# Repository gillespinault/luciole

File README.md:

# Luciole²

Lumières de vélo qui se parlent. Un essaim de petites unités (M5Stack NanoC6 ou AtomS3 Lite, ruban de LED SK6812) qui se découvrent par radio ESP-NOW longue portée, sans coordinateur ni réseau, et qui montrent d'un coup d'œil si on roule seul ou ensemble. Première sortie : Critical Mass de Bruxelles, 30 octobre 2026, avec les Merveilleux Fous Roulants.

| Dossier | Contenu |
|---|---|
| `firmware/` | Firmware ESP-IDF, une image par puce, nombre de LED en configuration. Voir `firmware/README.md`. |
| `web/` | Site public https://lucioles.limn-labs.xyz, publié par GitHub Pages à chaque push sur `main` : présentation, installation par USB depuis le navigateur (ESP Web Tools), page du maître `maitre/` (scènes : équipes, vote, jauge), page de mise au point `luciole/` (état en direct, graphes, réglages, enregistrement CSV, sur ordinateur et Android), simulation. |
| `sim/` | Simulation d'un Critical Mass : 20 000 vélos, 1 000 lucioles, mêmes règles que le firmware. Un fichier HTML, à ouvrir tel quel. |

Documentation du projet : wiki Outline, collection Luciole² (journal, décisions, architecture et contrat radio, matériel).

## Installer une luciole

Ouvrir https://lucioles.limn-labs.xyz dans Chrome ou Edge sur un ordinateur, brancher la luciole en USB, choisir le nombre de LED, cliquer sur Installer. Les mises à jour se font de la même façon.

En local, sans GitHub Pages : compiler (`firmware/README.md`), puis

```bash
python3 web/build.py --local          # assemble web/firmware/ (binaires, configurations NVS, manifestes)
python3 -m http.server 8766 --directory web
```

Web Serial exige HTTPS ou `localhost` : pour flasher depuis un autre poste, il faut passer par la page publiée.

## Régler une luciole sans la reflasher

https://lucioles.limn-labs.xyz/luciole/ : la luciole branchée en USB envoie son état en JSON (commande `stream`) et accepte `set clé valeur` pour chacun de ses 14 réglages, enregistrés en NVS. La page trace le signal des voisines, l'état, la phase, la radio et les ondes ; enregistre en CSV avec GPS ; gère des profils. Sur Android, elle parle à la luciole par WebUSB avec sa propre couche CDC (le Web Serial de Chrome Android ne sait pas ouvrir un appareil USB). Détail des commandes dans `firmware/README.md`.

## Faire évoluer le firmware sans casser l'essaim

Le contrat radio v1 (`firmware/main/luciole.h`, section « Contrat radio ») fixe le canal, le mode longue portée, le cycle de 2,5 s et le format des trames. Une luciole déjà distribuée doit rester membre de l'essaim : les nouveaux champs vont en fin de trame, les octets inconnus sont ignorés, la trame d'onde ne se remplace jamais. Le rendu (arc-en-ciel, cœur, couleurs, onde) est local et change librement. Vérifier les changements d'échelle dans `sim/index.html` avant de flasher.

## Licence

Luciole² est publié sous [CC BY-NC-SA 4.0](https://creativecommons.org/licenses/by-nc-sa/4.0/deed.fr) : réutilisation et modification libres avec attribution, partage à l'identique, pas d'usage commercial. Texte complet dans `LICENSE`.

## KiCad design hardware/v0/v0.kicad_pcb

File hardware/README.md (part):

# Cartes électroniques de Luciole²

Les cartes sont décrites par des scripts. Une commande reconstruit le schéma, la carte et les fichiers à déposer chez JLCPCB :

    tools/build.sh essai

Il faut Docker et l'image `kicad/kicad:10.0.8-full`. Le lanceur `tools/kicad` la désigne par son empreinte : la version de KiCad ne change pas tant que ce fichier ne change pas.

La spécification de la carte v0 et la méthode sont dans la collection Luciole² du wiki, pages « Carte Luciole² v0 » et « Conception de la carte v0 ».

## Dossiers

| Dossier | Contenu |
|---------|---------|
| `tools/` | La chaîne d'outils, commune à toutes les cartes |
| `lib/` | Les symboles et empreintes absents de la bibliothèque de KiCad, ou dont le brochage diffère. `build_lib.py` les écrit à partir des cotes des fiches techniques |
| `essai/` | Carte d'essai : trois LED entre deux connecteurs Grove, une pastille de test et un condensateur au dos. Elle a servi à valider la chaîne et la pose chez JLCPCB, et reste le banc de la chaîne |
| `v0/` | Carte v0, 122 × 28 mm, deux couches. La liste de connexions voulue et le schéma, révision 0.6, concordent : 160 composants, 85 réseaux. La carte est tracée en entier depuis le 18 novembre 2026 : `tools/build.sh v0` va au bout, sans liaison manquante ni alerte hors dérogations. Le tracé est figé dans `v0/routage.json`. Deux modèles l'ont relu le 18 novembre : huit corrections sont faites et contre-relues (dossier dans `v0/revue/`). Le brochage des 27 pièces autres que résistances et condensateurs a été relevé à l'aveugle dans les fiches des pièces commandées, et l'orientation de chaque pièce contrôlée dans l'aperçu de pose de JLCPCB. Le schéma a été comparé aux montages de référence et simulé, puis la carte confrontée aux retours d'expérience d'autres concepteurs. Rien n'est commandé |
| `fiches/` | Fiches techniques des fabricants et pièces de preuve. Gardées en local, non suivies par git ; `fiches/README.md` donne leurs sources |

## Les quatre fichiers d'une carte

Une carte est un dossier qui contient quatre fichiers écrits à la main.

`netlist_voulue.txt` donne les connexions voulues, par numéros de broches lus dans les fiches techniques. Il s'écrit avant le schéma. Une ligne qui commence par un espace continue le réseau de la ligne précédente.

`empreintes_voulues.txt` donne la géométrie voulue de chaque empreinte : le centre, la taille et le numéro de chaque pastille, relevés sur le plan du fabricant. Un boîtier normalisé pris dans la bibliothèque de KiCad s'y déclare `normalisé`, sans cotes.

`circuit.py` décrit le schéma, par noms de broches. Chaque broche doit être reliée à un réseau ou marquée `NC`, sinon la génération s'arrête. Elle s'arrête aussi quand deux composants sont posés si près que les fils de deux réseaux se touchent sur la page. Une empreinte sans pièce à poser (pastille de test, pont de soudure) se déclare avec `assemble=False`, une pièce prévue mais non montée avec `dnp=True`.

`carte.py` pose les composants et trace les pistes, en millimètres depuis le coin haut gauche de la carte. `flow()` range les petits composants d'un bloc dans un rectangle, `netclass()` donne leur largeur aux pistes d'alimentation. Un composant se pose au dos avec `bottom=True`. Son sens se vérifie par une assertion sur la position de ses pastilles, comme le fait la carte d'essai.

Les fichiers `.kicad_sch` et `.kicad_pcb` sont produits par ces scripts. Ils s'ouvrent dans KiCad pour la relecture. Une modification faite à la main dans KiCad est perdue à la construction suivante : elle se reporte dans le script.

## Étapes de la construction

1. Écriture de la bibliothèque du projet.
2. Écriture du schéma.
3. Contrôle électrique du schéma par KiCad.
4. Comparaison, broche par broche, de `netlist_voulue.txt` avec les connexions que KiCad exporte du schéma.
5. Comparaison, pastille par pastille, de `empreintes_voulues.txt` avec les fichiers d'empreintes.
6. Écriture de la carte à partir des connexions exportées.
7. Contrôle des règles de dessin par KiCad, avec la cohérence entre carte et schéma. KiCad remplit lui-même les plans de masse à cette étape. Toute alerte arrête la construction, sauf dérogation écrite dans `<projet>/derogations.txt`, avec sa raison ; `out/drc-compte-rendu.txt` sépare ce qui est ignoré de ce qui reste.
8. Export des fichiers de fabrication et des documents de relecture.

La construction s'arrête à la première étape qui échoue. L'étape 4 est celle qui attrape un symbole au mauvais brochage : le contrôle électrique de KiCad ne le voit pas. L'étape 5 attrape une empreinte mal numérotée ou mal cotée, que le contrôle des règles de dessin ne voit pas non plus dès que la carte est routée par réseau.

La pose d'une empreinte s'arrête aussi dans trois cas. Une pastille numérotée n'a pas de broche dans le schéma : c'est une plage thermique ou un blindage oubliés dans le symbole, ou alors une pastille à déclarer libre avec `free_pads`. Une broche laissée libre correspond à plusieurs pastilles de même numéro : il faut les relier à un réseau. Un symbole a plusieurs unités : la chaîne ne les gère pas, on dessine un symbole à une seule unité dans `lib/build_lib.py`.

Deux constructions de suite donnent les mêmes fichiers, à la date près dans les en-têtes.

Les fichiers KiCad du projet sont supprimés au début de chaque construction, fichier de projet compris. Un réglage fait à la main dans KiCad, comme la désactivation d'un contrôle, ne survit donc pas. Les verrous (`~projet.kicad_pro.lck`) sont supprimés aussi : un verrou resté d'une session interrompue fait croire à KiCad que le projet est ouvert ailleurs, il n'écrit alors plus le fichier de projet et la carte échoue à l'écriture des classes de réseaux.

## Routage

Le routage d'une carte se fait en deux temps, tous deux dans `carte.py`.

La structure se trace par script : liaisons longues, alimentations, convertisseur, sorties des boîtiers à pas fin. C'est elle qui décide si la carte est routable. L'en-tête de `v0/carte.py` décrit le plan retenu pour la carte v0.

Les petits composants sont posés par `tools/pose.py` : chacun va à la place libre la plus proche du cuivre que ses pastilles relient, dans l'orientation qui convient. Les ranger par rangées, sans regarder leurs connexions, donnait des blocs où tout devait se croiser.

Les liaisons courtes qui restent, autour de chaque bloc, sont tracées par le routeur sur grille `tools/maille.py`, puis figées dans `<projet>/routage.json` :

    tools/kicad python3 v0/carte.py --router
    tools/kicad python3 v0/carte.py --router --reseaux=EN,BOOT    # quelques réseaux, pour mettre au point un bloc

La construction normale rejoue ce fichier. Sa signature dit pour quelle carte il a été calculé : après un changement de placement ou de structure, la construction s'arrête et demande de relancer le routeur.

Le routeur sur grille applique nos règles d'isolement, sur une grille de 0,05 mm, à 45 degrés, sur deux faces. Quand une liaison ne passe pas, il défait les pistes qu'il a lui-même tracées et qui la barrent, la trace, puis retrace les réseaux défaits. Il ne touche jamais aux pistes tracées par script. Il redonne toujours le même tracé. Il signale les alimentations qu'il a dû tracer plus fin que leur classe. Une pastille ni rectangulaire ni ronde (pont de soudure, pastille aux coins arrondis) est prise avec son contour exact : une piste arrêtée dans un coin de son rectangle englobant n'y est pas reliée, pour KiCad.

Une fois la carte tracée, `carte.py` fait deux finitions, à chaque construction.

La masse d'abord. Sur deux couches, chaque piste coupe un plan, et les deux plans finissent en morceaux. `Board.stitch_zones()` regroupe les morceaux déjà reliés entre eux, puis pose un via là où un morceau isolé recouvre le plan principal de l'autre face. Un morceau sans recouvrement est enfermé entre des pistes : `Router.tie()` relie alors une de ses pastilles au cuivre de masse principal, comme le routeur trace un signal, par l'une ou l'autre face. Ce qui reste isolé après cela est affiché, avec ses pastilles : c'est une poche sans issue, qui se règle dans la structure, en donnant un via de masse au composant avant le routage.

L'ébarbage ensuite. La structure propose des accès que le routeur n'utilise pas tous : un via au bout d'une voie, une sortie devant une pastille à pas fin. `Board.trim()` demande à KiCad quels bouts de piste et quels vias sont pendants, par le test de son propre contrôle. Il raccourcit la piste jusqu'à son dernier raccord, ou la retire. Avant de retirer un via relié sur une seule face, il prolonge jusqu'à son centre les pistes qui finissaient dans sa pastille : c'est le cuivre du via qui les reliait. `--sans-ebarbage` saute cette étape, pour regarder la carte avant.

Pour voir un blocage, `tools/vue.py` dessine une zone de la carte avec le nom du réseau sur chaque pastille :

    tools/kicad python3 tools/vue.py v0/v0.kicad_pcb 92 13 117 28 --face=F --reseaux=PORT_PU,IO2
    tools/kicad python3 tools/vue.py v0/v0.kicad_pcb 19 19 40 28 --face=B --plans

`--reseaux` met ces réseaux en couleurs vives, `--plans` dessine le cuivre des plans de masse : un morceau isolé s'y voit tout de suite.

Pour comparer des variantes sans toucher au projet, `v0/carte.py` accepte des options d'essai. Avec l'une d'elles, la carte et son tracé s'écrivent dans `v0/out/`, sous un nom qui dit la variante ; plusieurs essais peuvent tourner en même temps.

    tools/kicad python3 v0/carte.py --router --largeur=28 --graine=7

| Option | Effet |
|--------|-------|
| `--largeur=28` | Largeur de la carte. Elle s'élargit par le bas : la rangée de LED, le module et les connecteurs gardent leur place |
| `--graine=7` | Autre ordre de passage du routeur. Chaque graine donne un autre tracé ; une graine donnée redonne le même |
| `--ecart=0.35` | Écart que le poseur laisse entre deux composants (0,2 mm par défaut) |
| `--dos=1` | Surcoût d'une piste nouvelle au dos, sous la batterie (3 par défaut) |
| `--sans=SW1,SW2` | Ne pose pas ces composants, pour mesurer ce que leur retrait libère sans toucher au schéma |

`--graine` seule n'ouvre pas le mode d'essai : elle sert aussi à tracer la carte du projet avec l'ordre retenu.

### Ce que les essais du 18 novembre 2026 ont appris

- La largeur compte plus que tout le reste. Avec toutes les fonctions, le routeur laisse 26 liaisons à 22 mm, 19 à 24 mm, 15 à 26 mm, 5 à 28 mm et 4 à 30 mm. La carte est passée à 28 mm.
- Retirer les boutons internes ne change rien. Lever le surcoût du dos non plus : les blocs qui coincent sont là où le dos est déjà pris. Un écart du poseur de 0,35 ou 0,5 mm fait moins bien que 0,2 mm.
- Lancer le routeur avec une douzaine de graines dit où chercher. Une liaison qui échoue à un endroit différent selon la graine relève de l'ordre de passage. Un réseau qui échoue à toutes les graines désigne une erreur de structure : une piste tracée par script qui enferme d'autres signaux. La commande du convertisseur, tracée en face avant devant le module, enfermait ainsi la donnée des LED et les sorties de la colonne de gauche ; elle passe maintenant au dos, dans le faisceau.
- Une protection à deux pastilles par ligne (USBLC6) se relie sous son boîtier, par script. Laissé seul, le routeur y croisait les deux lignes.
- Le poseur ne remplace pas un plan de bloc. Il met chaque composant au plus près de son cuivre, sans voir l'ordre dans lequel les signaux arrivent. Autour d'un transistor ou d'un circuit, les broches se suivent toujours dans le même sens : si les pistes arrivent dans l'autre, il faut un croisement, donc un via, et il n'y a pas toujours la place. Les blocs où plusieurs signaux se partagent quelques composants sont donc posés et reliés par script : port côté module, USB, protecteur du port, résistances du chargeur, ponts de mesure. Le lot de douze graines est passé de zéro tracé complet à douze sur douze, et de vingt minutes à trois.
- Des voies qui remontent côte à côte forment un nid : de l'intérieur, seule la plus intérieure est accessible. Chaque voie du faisceau finit maintenant là où est son composant.
- Entre deux lignes qui traversent un composant, ce qui est au milieu est enfermé. Pour un protecteur USBLC6, c'est sa broche de masse d'un côté et sa broche d'alimentation de l'autre : il leur faut un via chacune, à un endroit où l'autre face est libre.
- L'USB-C et le Grove sont dos à dos : entre eux, presque aucun via n'est possible. Le bloc de l'USB est tracé pour s'en passer, et les broches CC passent sous la coque du connecteur.
- Une piste d'alimentation tracée en face avant coupe la bande qu'elle traverse. Les signaux qui doivent la franchir passent par le dos ; il faut donc y garder un passage libre, et y ranger les voies au ras du faisceau.
- La zone de garde du module radio a la forme d'un T, boîtier puis zone d'antenne. Prise pour un rectangle, elle interdisait tout le coin de la carte au poseur : `Board.courtyard_boxes()` la découpe suivant ses arêtes.
- La largeur de 28 mm a libéré deux zones que les régions du poseur, écrites pour 22 mm, n'utilisaient pas : sous le coin du module, sur les deux faces, et le milieu de la bande du bas.

### Ce que la revue du routage du 18 novembre 2026 a appris

Le tri complet est dans le wiki, page « Revue du routage du 18 novembre 2026 ».

- Le contrôle des règles ne voit pas les chemins. Un circuit de puissance sans via sous sa plage thermique, une ligne qui se sépare avant sa protection, un condensateur d'alimentation à 59 mm de la broche qu'il découple : tout cela passait le contrôle.
- Une protection contre les décharges se traverse. La ligne entre par une broche et repart de l'autre. Si elle se sépare avant, la décharge prend aussi le chemin qui évite la protection.
- Un circuit de puissance qui chauffe reçoit ses vias sous sa plage centrale au moment où on le pose, pas après.
- Poser par script les petits composants d'une commande de grille. Laissés au poseur, ceux de la protection contre l'inversion avaient donné 36 mm de piste et six vias pour deux pastilles distantes de 10 mm.
- Une piste courte entre deux grandes pastilles ne chauffe presque pas : la chaleur part par ses deux bouts. Les abaques de largeur supposent une piste longue. Chiffrer avant de redessiner un bloc.
- Toute piste ajoutée en face avant peut fermer une poche du plan de masse. Le compte des groupes restés isolés, à la fin de chaque essai, l'a signalé aux douze graines pour une correction mal placée.
- Un relecteur se trompe aussi. Sur trente constats, trois reposaient sur une lecture fausse des pièces ou de la nomenclature. Chaque constat se vérifie sur la carte avant d'être corrigé.

### Simulations

    v0/simu/lancer.sh            alimentation : inversion de la batterie, partage USB/batterie, chargeur
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
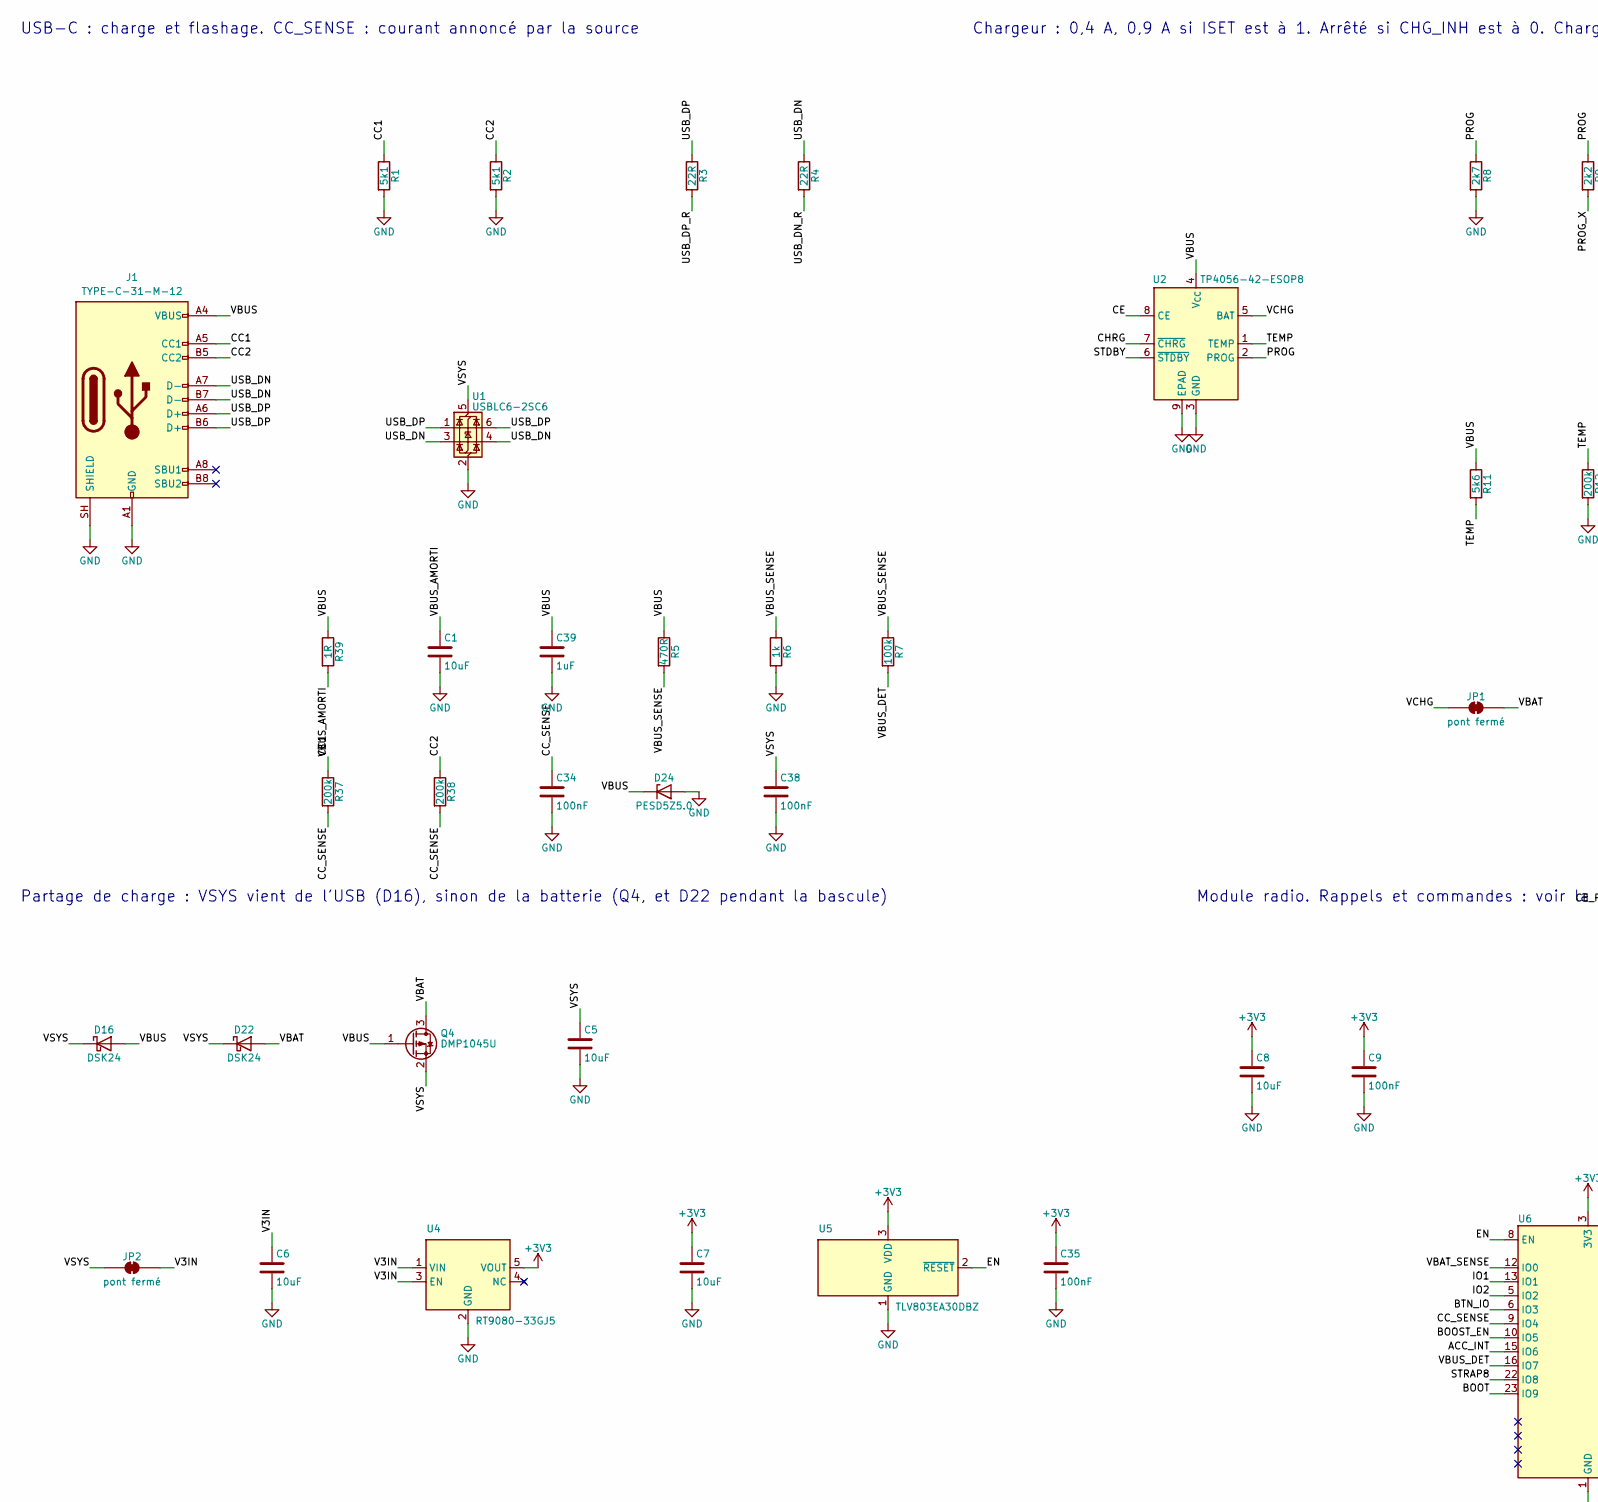
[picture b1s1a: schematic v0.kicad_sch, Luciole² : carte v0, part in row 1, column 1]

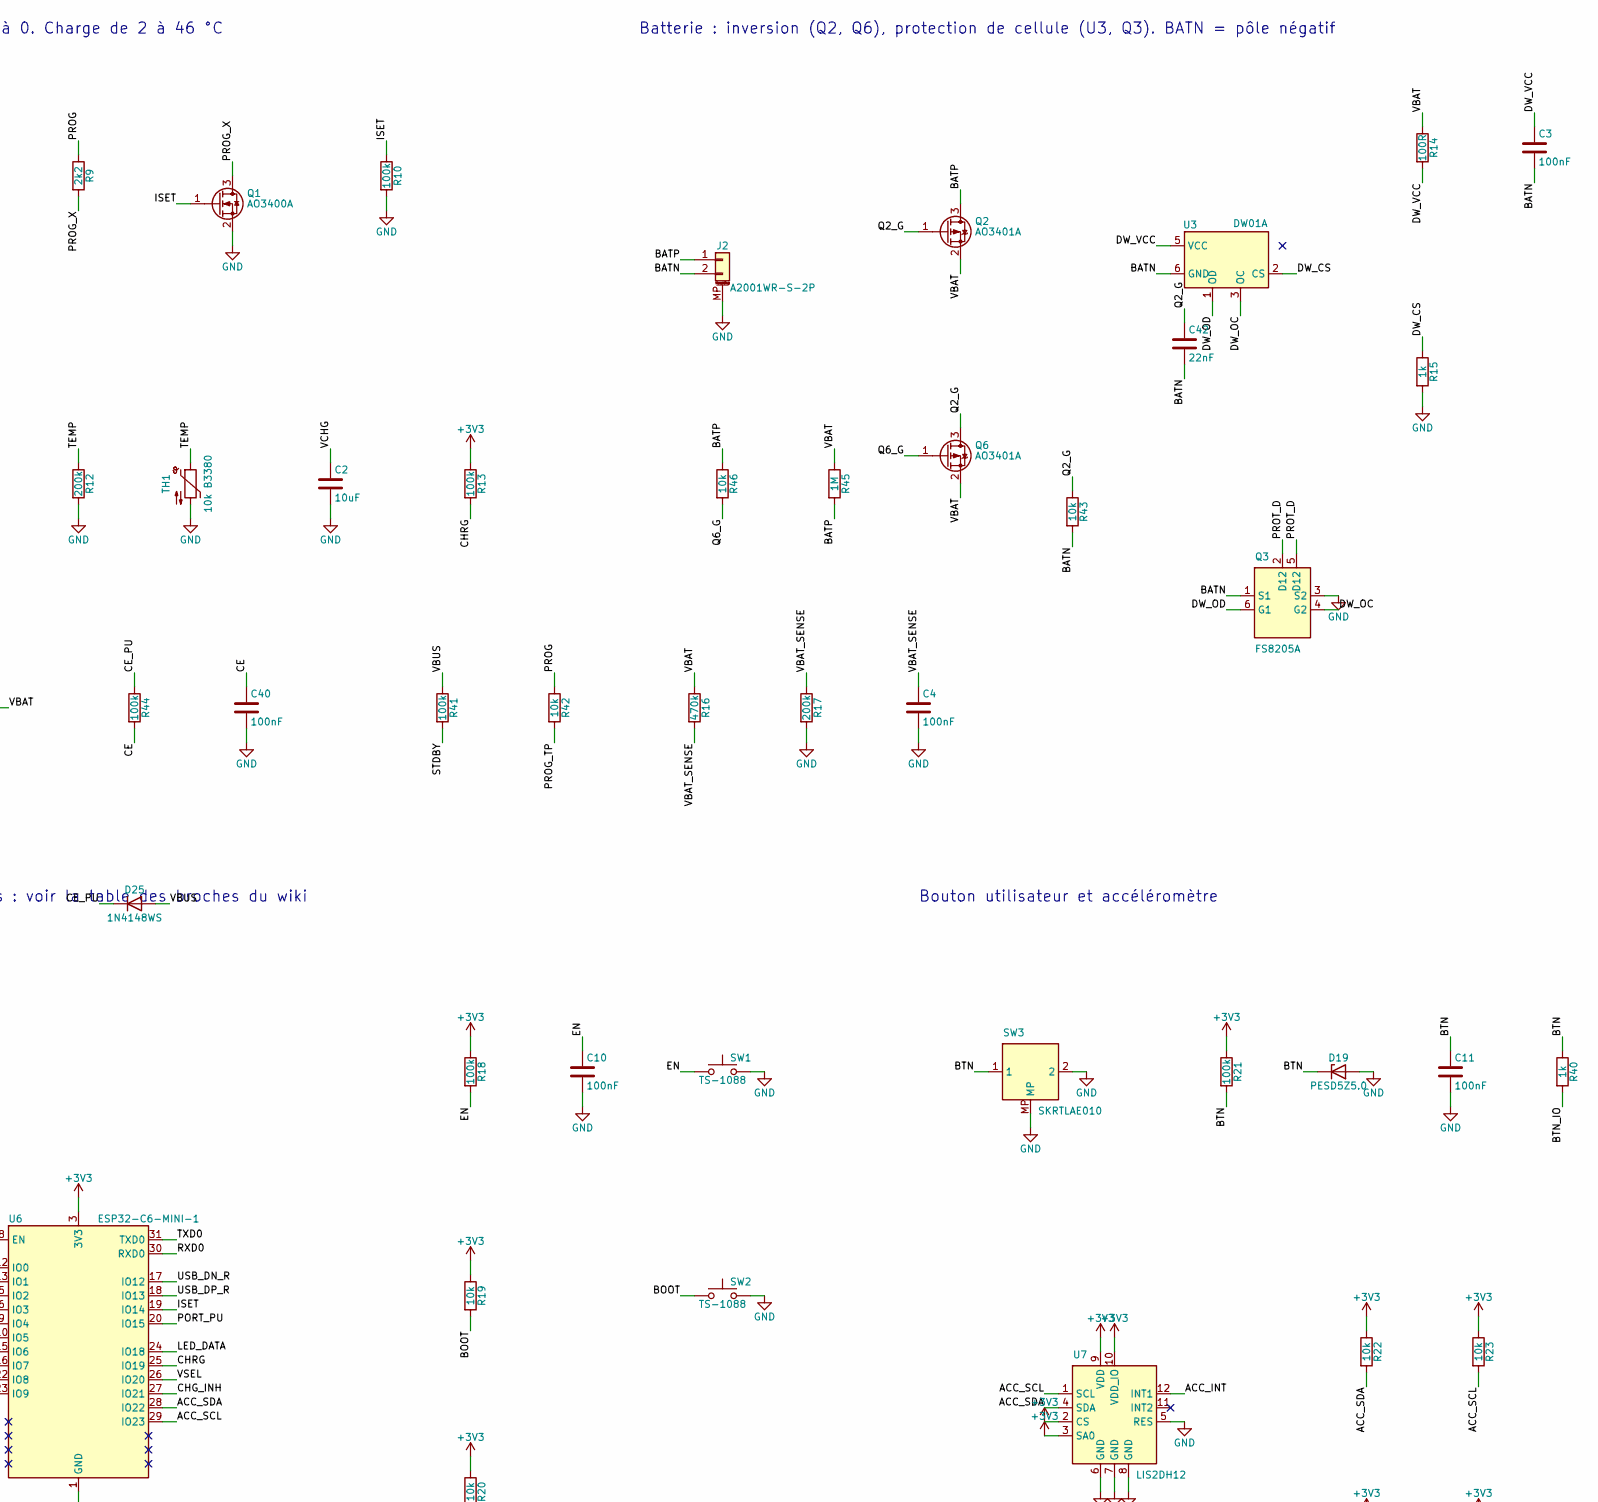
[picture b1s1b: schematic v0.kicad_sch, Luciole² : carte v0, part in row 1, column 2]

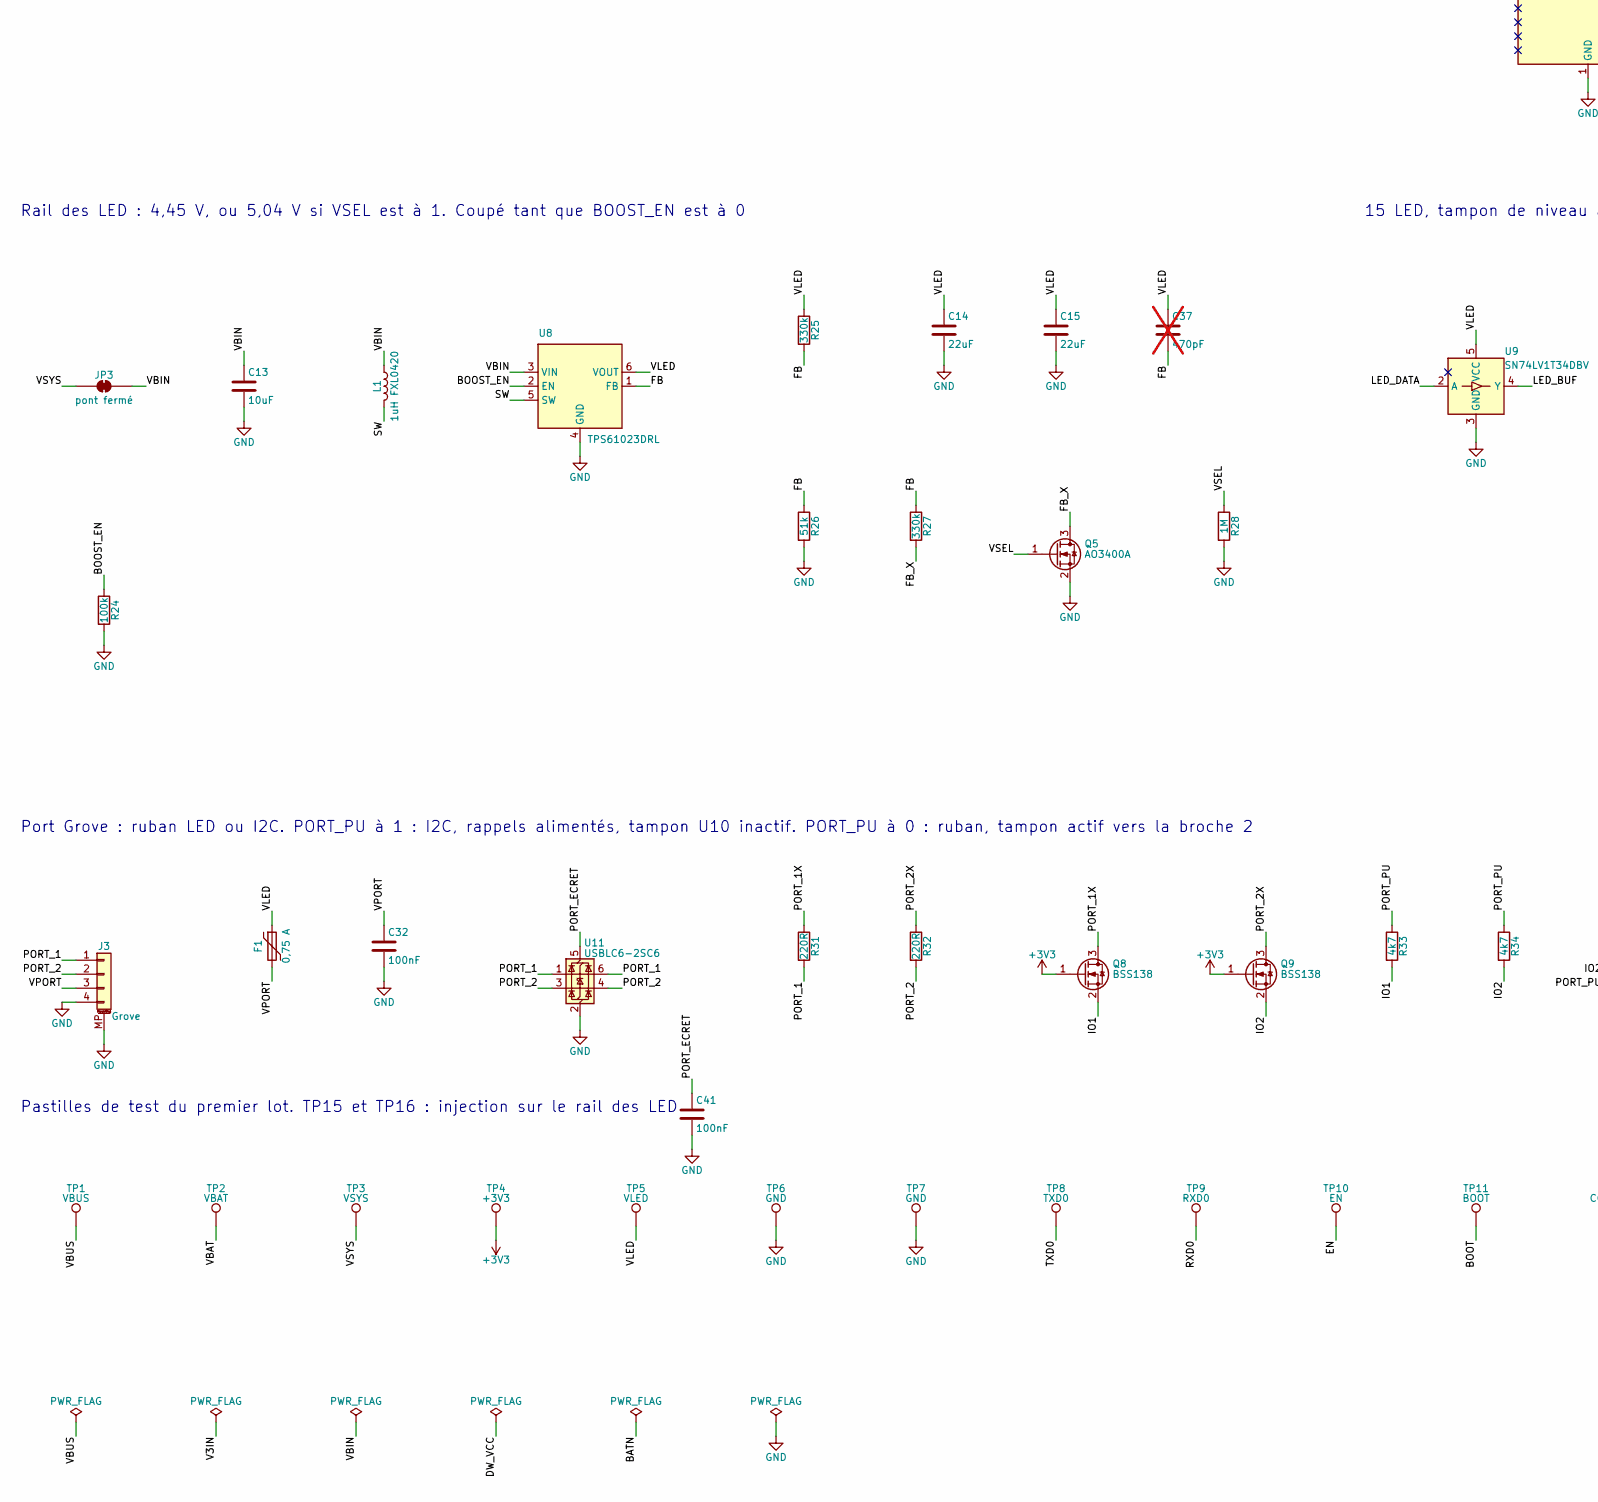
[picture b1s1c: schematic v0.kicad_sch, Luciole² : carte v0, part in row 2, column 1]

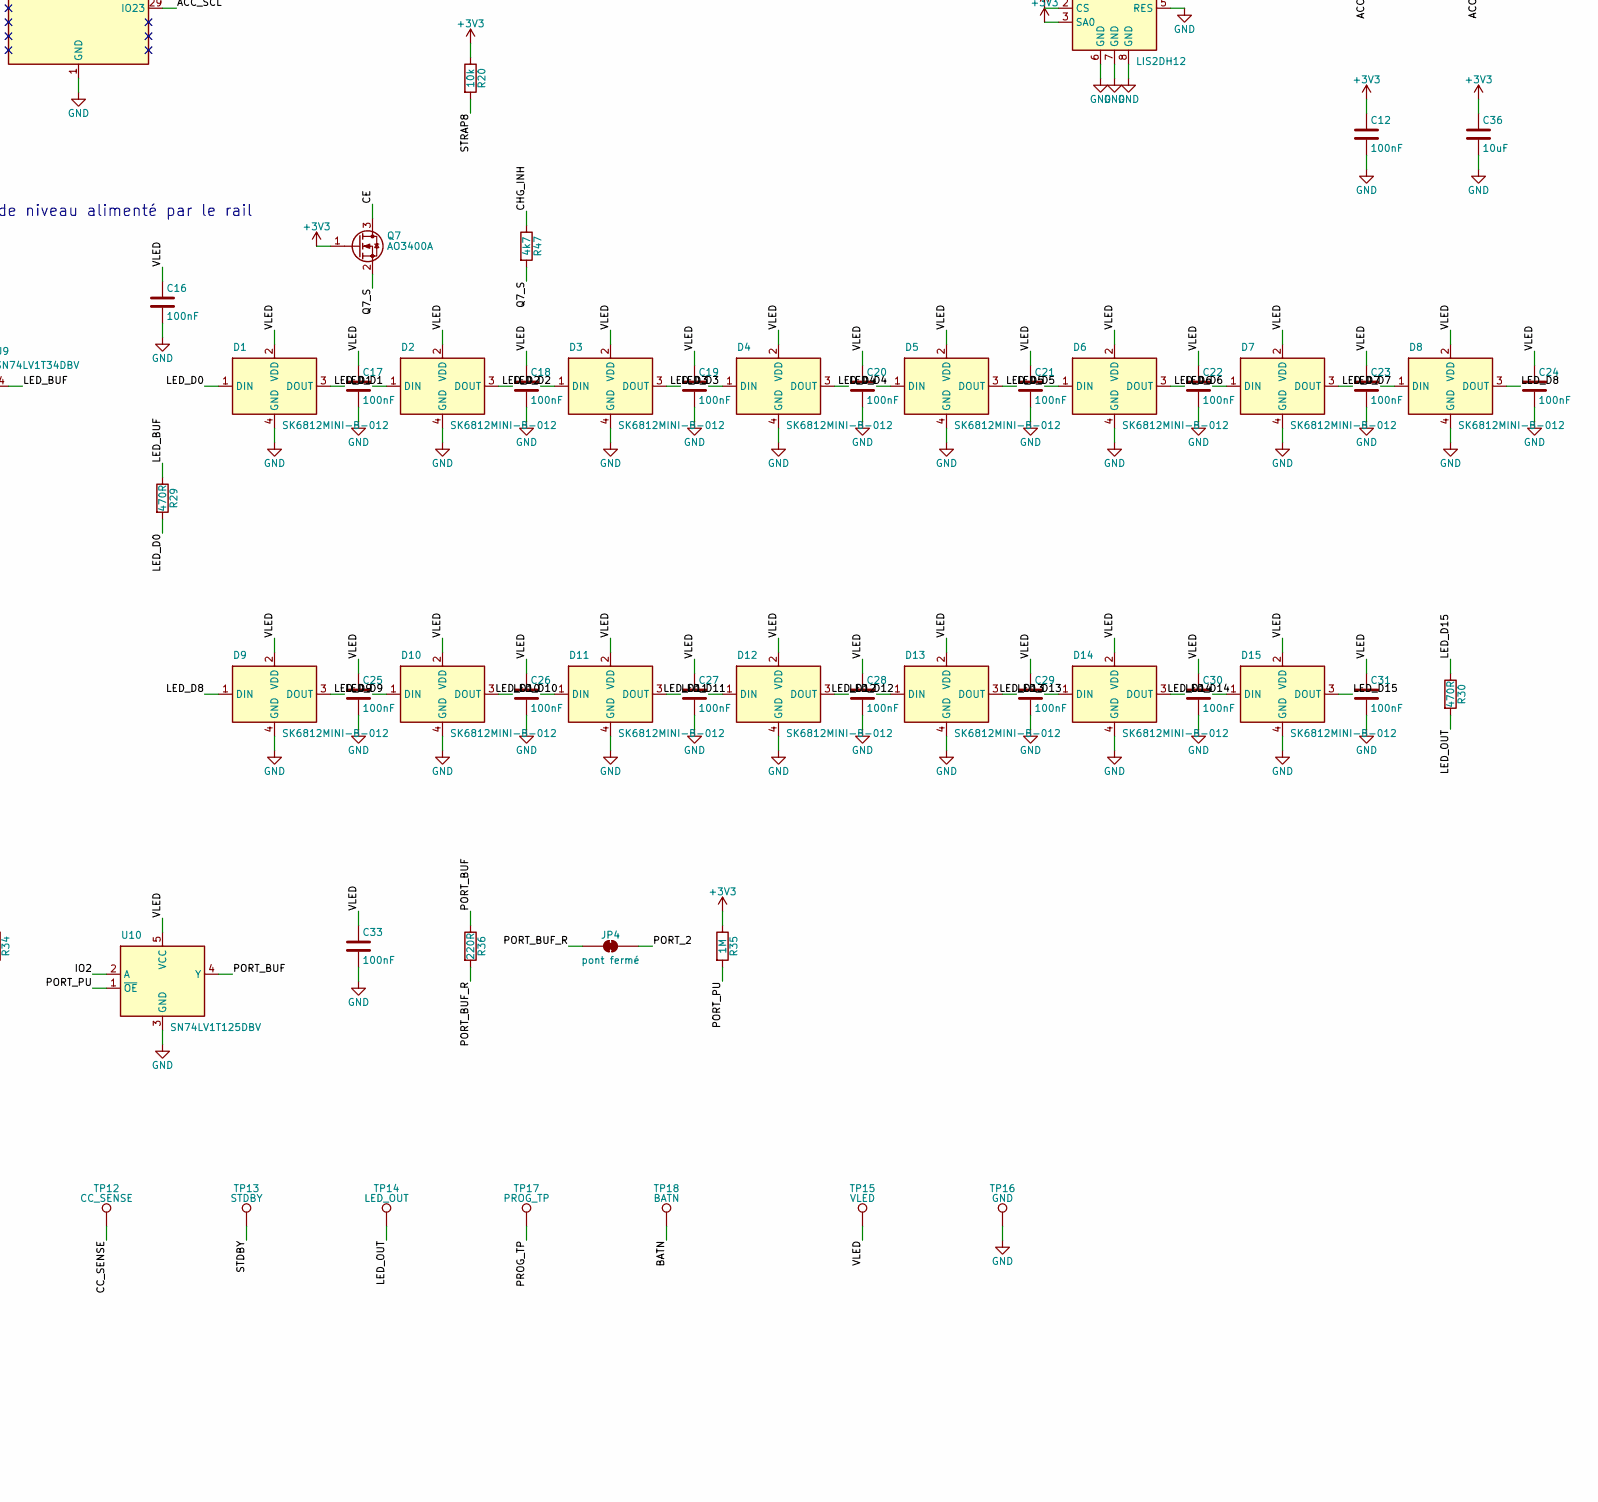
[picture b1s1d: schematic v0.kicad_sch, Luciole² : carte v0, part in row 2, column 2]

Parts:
C1, C2, C5, C6, C7, C8, C13, C36: 10uF; C_0603_1608Metric; LCSC C19702
C3, C4, C9, C10, C11, C12, C16, C17, C18, C19, C20, C21, C22, C23, C24, C25, C26, C27, C28, C29, C30, C31, C32, C33, C34, C35, C38, C40, C41: 100nF; C_0402_1005Metric; LCSC C1525
C14, C15: 22uF; C_0805_2012Metric; LCSC C45783
C37: 470pF; C_0402_1005Metric; LCSC C1537; not fitted
C39: 1uF; C_0402_1005Metric; LCSC C52923
C42: 22nF; C_0402_1005Metric; LCSC C1532
D1, D2, D3, D4, D5, D6, D7, D8, D9, D10, D11, D12, D13, D14, D15: SK6812MINI-B-012; LED_OPSCO_SK6812MINI-B-012_3.7x3.5mm; LCSC C5183448
D16, D22: DSK24; D_SOD-123F; LCSC C22466352
D19, D24: PESD5Z5.0; D_SOD-523; LCSC C132368
D25: 1N4148WS; D_SOD-323; LCSC C2128
F1: 0,75 A; Fuse_1206_3216Metric; LCSC C269118
J1: TYPE-C-31-M-12; USB_C_Receptacle_HRO_TYPE-C-31-M-12; LCSC C165948
J2: A2001WR-S-2P; JST_PH_S2B-PH-SM4-TB_1x02-1MP_P2.00mm_Horizontal; LCSC C225233
J3: Grove; Grove_HY2.0-4P_Megastar_ZX-HY2.0-4PWT_Horizontal; LCSC C7429571
JP1, JP2, JP3, JP4: pont fermé; SolderJumper-2_P1.3mm_Bridged_RoundedPad1.0x1.5mm
L1: 1uH FXL0420; L_cjiang_FXL0420; LCSC C167203
Q1, Q5, Q7: AO3400A; SOT-23; LCSC C20917
Q2, Q6: AO3401A; SOT-23; LCSC C15127
Q3: FS8205A; SOT-23-6; LCSC C2830320
Q4: DMP1045U; SOT-23; LCSC C177033
Q8, Q9: BSS138; SOT-23; LCSC C7420339
R1, R2: 5k1; R_0402_1005Metric; LCSC C25905
R3, R4: 22R; R_0402_1005Metric; LCSC C25092
R5, R29, R30: 470R; R_0402_1005Metric; LCSC C25117
R6, R15, R40: 1k; R_0402_1005Metric; LCSC C11702
R7, R10, R13, R18, R21, R24, R41, R44: 100k; R_0402_1005Metric; LCSC C25741
R8: 2k7; R_0603_1608Metric; LCSC C13167
R9: 2k2; R_0402_1005Metric; LCSC C25879
R11: 5k6; R_0402_1005Metric; LCSC C25908
R12, R17, R37, R38: 200k; R_0402_1005Metric; LCSC C25764
R14: 100R; R_0402_1005Metric; LCSC C25076
R16: 470k; R_0402_1005Metric; LCSC C25790
R19, R20, R22, R23, R42, R43, R46: 10k; R_0402_1005Metric; LCSC C25744
R25, R27: 330k; R_0402_1005Metric; LCSC C25778
R26: 51k; R_0402_1005Metric; LCSC C25794
R28, R35, R45: 1M; R_0402_1005Metric; LCSC C26083
R31, R32, R36: 220R; R_0402_1005Metric; LCSC C25091
R33, R34, R47: 4k7; R_0402_1005Metric; LCSC C25900
R39: 1R; R_0603_1608Metric; LCSC C22936
SW1, SW2: TS-1088; SW_SPST_TS-1088-xR020; LCSC C720477
SW3: SKRTLAE010; SW_Push_1P1T-MP_NO_Horizontal_Alps_SKRTLAE010; LCSC C110293
TH1: 10k B3380; R_0402_1005Metric; LCSC C77131
TP1: VBUS; TestPoint_Pad_D1.5mm
TP2: VBAT; TestPoint_Pad_D1.5mm
TP3: VSYS; TestPoint_Pad_D1.5mm
TP4: +3V3; TestPoint_Pad_D1.5mm
TP5: VLED; TestPoint_Pad_D1.5mm
TP6, TP7: GND; TestPoint_Pad_D1.5mm
TP8: TXD0; TestPoint_Pad_D1.5mm
TP9: RXD0; TestPoint_Pad_D1.5mm
TP10: EN; TestPoint_Pad_D1.5mm
TP11: BOOT; TestPoint_Pad_D1.5mm
TP12: CC_SENSE; TestPoint_Pad_D1.5mm
TP13: STDBY; TestPoint_Pad_D1.5mm
TP14: LED_OUT; TestPoint_Pad_D1.5mm
TP15: VLED; TestPoint_Pad_D2.0mm
TP16: GND; TestPoint_Pad_D2.0mm
TP17: PROG_TP; TestPoint_Pad_D1.5mm
TP18: BATN; TestPoint_Pad_D1.5mm
U1, U11: USBLC6-2SC6; SOT-23-6; LCSC C7519
U2: TP4056-42-ESOP8; SOIC-8-1EP_3.9x4.9mm_P1.27mm_EP2.41x3.3mm; LCSC C16581
U3: DW01A; SOT-23-6; LCSC C351410
U4: RT9080-33GJ5; TSOT-23-5; LCSC C841192
U5: TLV803EA30DBZ; SOT-23; LCSC C5218924
U6: ESP32-C6-MINI-1; LCSC C5736265
U7: LIS2DH12; LGA-12_2x2mm_P0.5mm; LCSC C110926
U8: TPS61023DRL; SOT-563; LCSC C919459
U9: SN74LV1T34DBV; SOT-23-5; LCSC C100024
U10: SN74LV1T125DBV; SOT-23-5; LCSC C51886115

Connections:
+3V3: C7.1, C8.1, C9.1, C12.1, C35.1, C36.1, Q7.1 (G), Q8.1 (G), Q9.1 (G), R13.1, R18.1, R19.1, R20.1, R21.1, R22.1, R23.1, R35.1, TP4.1, U4.5 (VOUT), U5.3 (VDD), U6.3 (3V3), U7.2 (CS), U7.3 (SA0), U7.9 (VDD), U7.10 (VDD_IO)
/ACC_INT: U6.15 (IO6), U7.12 (INT1)
/ACC_SCL: R23.2, U6.29 (IO23), U7.1 (SCL)
/ACC_SDA: R22.2, U6.28 (IO22), U7.4 (SDA)
/BATN: C3.2, C42.2, J2.2, Q3.1 (S1), R43.2, TP18.1, U3.6 (GND)
/BATP: J2.1, Q2.3 (D), R45.2, R46.1
/BOOST_EN: R24.1, U6.10 (IO5), U8.2 (EN)
/BOOT: R19.2, SW2.1, TP11.1, U6.23 (IO9)
/BTN: C11.1, D19.1 (K), R21.2, R40.1, SW3.1
/BTN_IO: R40.2, U6.6 (IO3)
/CC1: J1.A5 (CC1), R1.1, R37.1
/CC2: J1.B5 (CC2), R2.1, R38.1
/CC_SENSE: C34.1, R37.2, R38.2, TP12.1, U6.9 (IO4)
/CE: C40.1, Q7.3 (D), R44.2, U2.8 (CE)
/CE_PU: D25.1 (K), R44.1
/CHG_INH: R47.1, U6.27 (IO21)
/CHRG: R13.2, U2.7 (~CHRG), U6.25 (IO19)
/DW_CS: R15.1, U3.2 (CS)
/DW_OC: Q3.4 (G2), U3.3 (OC)
/DW_OD: Q3.6 (G1), U3.1 (OD)
/DW_VCC: C3.1, R14.2, U3.5 (VCC)
/EN: C10.1, R18.2, SW1.1, TP10.1, U5.2 (~RESET), U6.8 (EN)
/FB: C37.2, R25.2, R26.1, R27.1, U8.1 (FB)
/FB_X: Q5.3 (D), R27.2
/IO1: Q8.2 (S), R33.2, U6.13 (IO1)
/IO2: Q9.2 (S), R34.2, U6.5 (IO2), U10.2 (A)
/ISET: Q1.1 (G), R10.1, U6.19 (IO14)
/LED_BUF: R29.1, U9.4 (Y)
/LED_D0: D1.1 (DIN), R29.2
/LED_D1: D1.3 (DOUT), D2.1 (DIN)
/LED_D2: D2.3 (DOUT), D3.1 (DIN)
/LED_D3: D3.3 (DOUT), D4.1 (DIN)
/LED_D4: D4.3 (DOUT), D5.1 (DIN)
/LED_D5: D5.3 (DOUT), D6.1 (DIN)
/LED_D6: D6.3 (DOUT), D7.1 (DIN)
/LED_D7: D7.3 (DOUT), D8.1 (DIN)
/LED_D8: D8.3 (DOUT), D9.1 (DIN)
/LED_D9: D9.3 (DOUT), D10.1 (DIN)
/LED_D10: D10.3 (DOUT), D11.1 (DIN)
/LED_D11: D11.3 (DOUT), D12.1 (DIN)
/LED_D12: D12.3 (DOUT), D13.1 (DIN)
/LED_D13: D13.3 (DOUT), D14.1 (DIN)
/LED_D14: D14.3 (DOUT), D15.1 (DIN)
/LED_D15: D15.3 (DOUT), R30.1
/LED_DATA: U6.24 (IO18), U9.2 (A)
/LED_OUT: R30.2, TP14.1
/PORT_1: J3.1, R31.2, U11.1 (I/O1), U11.6 (I/O1)
/PORT_1X: Q8.3 (D), R31.1
/PORT_2: J3.2, JP4.2 (B), R32.2, U11.3 (I/O2), U11.4 (I/O2)
/PORT_2X: Q9.3 (D), R32.1
/PORT_BUF: R36.1, U10.4 (Y)
/PORT_BUF_R: JP4.1 (A), R36.2
/PORT_ECRET: C41.1, U11.5 (VBUS)
/PORT_PU: R33.1, R34.1, R35.2, U6.20 (IO15), U10.1 (~OE)
/PROG: R8.1, R9.1, R42.1, U2.2 (PROG)
/PROG_TP: R42.2, TP17.1
/PROG_X: Q1.3 (D), R9.2
/PROT_D: Q3.2 (D12), Q3.5 (D12)
/Q2_G: C42.1, Q2.1 (G), Q6.3 (D), R43.1
/Q6_G: Q6.1 (G), R46.2
/Q7_S: Q7.2 (S), R47.2
/RXD0: TP9.1, U6.30 (RXD0)
/STDBY: R41.2, TP13.1, U2.6 (~STDBY)
/STRAP8: R20.2, U6.22 (IO8)
/SW: L1.2, U8.5 (SW)
/TEMP: R11.2, R12.1, TH1.1, U2.1 (TEMP)
/TXD0: TP8.1, U6.31 (TXD0)
/USB_DN: J1.A7 (D-), J1.B7 (D-), R4.1, U1.3 (I/O2), U1.4 (I/O2)
/USB_DN_R: R4.2, U6.17 (IO12)
/USB_DP: J1.A6 (D+), J1.B6 (D+), R3.1, U1.1 (I/O1), U1.6 (I/O1)
/USB_DP_R: R3.2, U6.18 (IO13)
/V3IN: C6.1, JP2.2 (B), U4.1 (VIN), U4.3 (EN)
/VBAT: D22.2 (A), JP1.2 (B), Q2.2 (S), Q4.3 (D), Q6.2 (S), R14.1, R16.1, R45.1, TP2.1
/VBAT_SENSE: C4.1, R16.2, R17.1, U6.12 (IO0)
/VBIN: C13.1, JP3.2 (B), L1.1, U8.3 (VIN)
/VBUS: C39.1, D16.2 (A), D24.1 (K), D25.2 (A), J1.A4 (VBUS), J1.A9 (VBUS), J1.B4 (VBUS), J1.B9 (VBUS), Q4.1 (G), R5.1, R11.1, R39.1, R41.1, TP1.1, U2.4 (V_{CC})
/VBUS_AMORTI: C1.1, R39.2
/VBUS_DET: R7.2, U6.16 (IO7)
/VBUS_SENSE: R5.2, R6.1, R7.1
/VCHG: C2.1, JP1.1 (A), U2.5 (BAT)
/VLED: C14.1, C15.1, C16.1, C17.1, C18.1, C19.1, C20.1, C21.1, C22.1, C23.1, C24.1, C25.1, C26.1, C27.1, C28.1, C29.1, C30.1, C31.1, C33.1, C37.1, D1.2 (VDD), D2.2 (VDD), D3.2 (VDD), D4.2 (VDD), D5.2 (VDD), D6.2 (VDD), D7.2 (VDD), D8.2 (VDD), D9.2 (VDD), D10.2 (VDD), D11.2 (VDD), D12.2 (VDD), D13.2 (VDD), D14.2 (VDD), D15.2 (VDD), F1.1, R25.1, TP5.1, TP15.1, U8.6 (VOUT), U9.5 (VCC), U10.5 (VCC)
/VPORT: C32.1, F1.2, J3.3
/VSEL: Q5.1 (G), R28.1, U6.26 (IO20)
/VSYS: C5.1, C38.1, D16.1 (K), D22.1 (K), JP2.1 (A), JP3.1 (A), Q4.2 (S), TP3.1, U1.5 (VBUS)
GND: C1.2, C2.2, C4.2, C5.2, C6.2, C7.2, C8.2, C9.2, C10.2, C11.2, C12.2, C13.2, C14.2, C15.2, C16.2, C17.2, C18.2, C19.2, C20.2, C21.2, C22.2, C23.2, C24.2, C25.2, C26.2, C27.2, C28.2, C29.2, C30.2, C31.2, C32.2, C33.2, C34.2, C35.2, C36.2, C38.2, C39.2, C40.2, C41.2, D1.4 (GND), D2.4 (GND), D3.4 (GND), D4.4 (GND), D5.4 (GND), D6.4 (GND), D7.4 (GND), D8.4 (GND), D9.4 (GND), D10.4 (GND), D11.4 (GND), D12.4 (GND), D13.4 (GND), D14.4 (GND), D15.4 (GND), D19.2 (A), D24.2 (A), J1.A1 (GND), J1.A12 (GND), J1.B1 (GND), J1.B12 (GND), J1.SH (SHIELD), J2.MP (MountPin), J3.4, J3.MP (MountPin), Q1.2 (S), Q3.3 (S2), Q5.2 (S), R1.2, R2.2, R6.2, R8.2, R10.2, R12.2, R15.2, R17.2, R24.2, R26.2, R28.2, SW1.2, SW2.2, SW3.2, SW3.MP, TH1.2, TP6.1, TP7.1, TP16.1, U1.2 (GND), U2.3 (GND), U2.9 (EPAD), U4.2 (GND), U5.1 (GND), U6.1 (GND), U6.2 (GND), U6.11 (GND), U6.14 (GND), U6.36 (GND), U6.37 (GND), U6.38 (GND), U6.39 (GND), U6.40 (GND), U6.41 (GND), U6.42 (GND), U6.43 (GND), U6.44 (GND), U6.45 (GND), U6.46 (GND), U6.47 (GND), U6.48 (GND), U6.49 (GND), U6.50 (GND), U6.51 (GND), U6.52 (GND), U6.53 (GND), U7.5 (RES), U7.6 (GND), U7.7 (GND), U7.8 (GND), U8.4 (GND), U9.3 (GND), U10.3 (GND), U11.2 (GND)

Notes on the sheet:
USB-C : charge et flashage. CC_SENSE : courant annoncé par la source
Chargeur : 0,4 A, 0,9 A si ISET est à 1. Arrêté si CHG_INH est à 0. Charge de 2 à 46 °C
Batterie : inversion (Q2, Q6), protection de cellule (U3, Q3). BATN = pôle négatif
Partage de charge : VSYS vient de l'USB (D16), sinon de la batterie (Q4, et D22 pendant la bascule)
Module radio. Rappels et commandes : voir la table des broches du wiki
Bouton utilisateur et accéléromètre
Rail des LED : 4,45 V, ou 5,04 V si VSEL est à 1. Coupé tant que BOOST_EN est à 0
15 LED, tampon de niveau alimenté par le rail
Port Grove : ruban LED ou I2C. PORT_PU à 1 : I2C, rappels alimentés, tampon U10 inactif. PORT_PU à 0 : ruban, tampon actif vers la broche 2
Pastilles de test du premier lot. TP15 et TP16 : injection sur le rail des LED

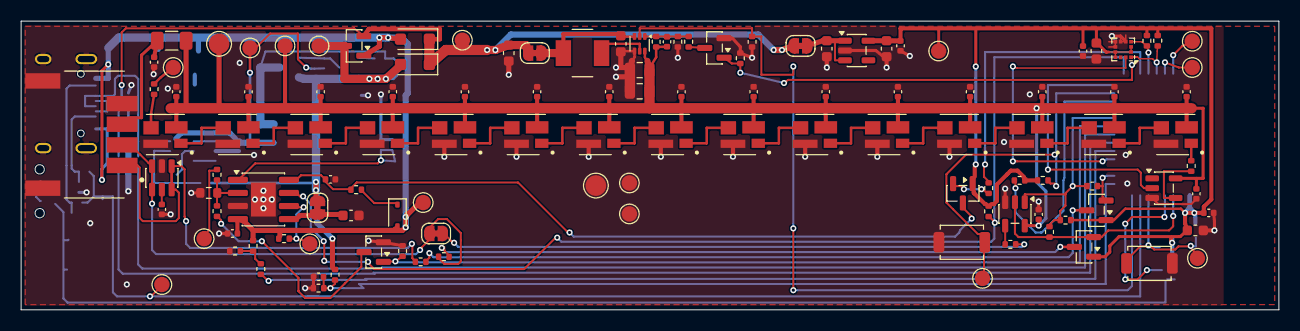
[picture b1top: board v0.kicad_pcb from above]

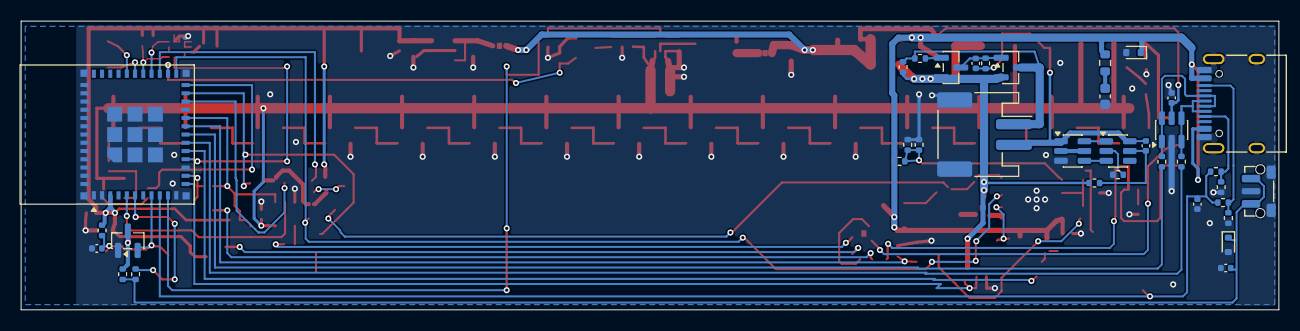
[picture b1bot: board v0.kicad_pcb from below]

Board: 2 copper layers, 122.0 x 28.0 mm, 160 parts (37 on the bottom side), 85 nets.

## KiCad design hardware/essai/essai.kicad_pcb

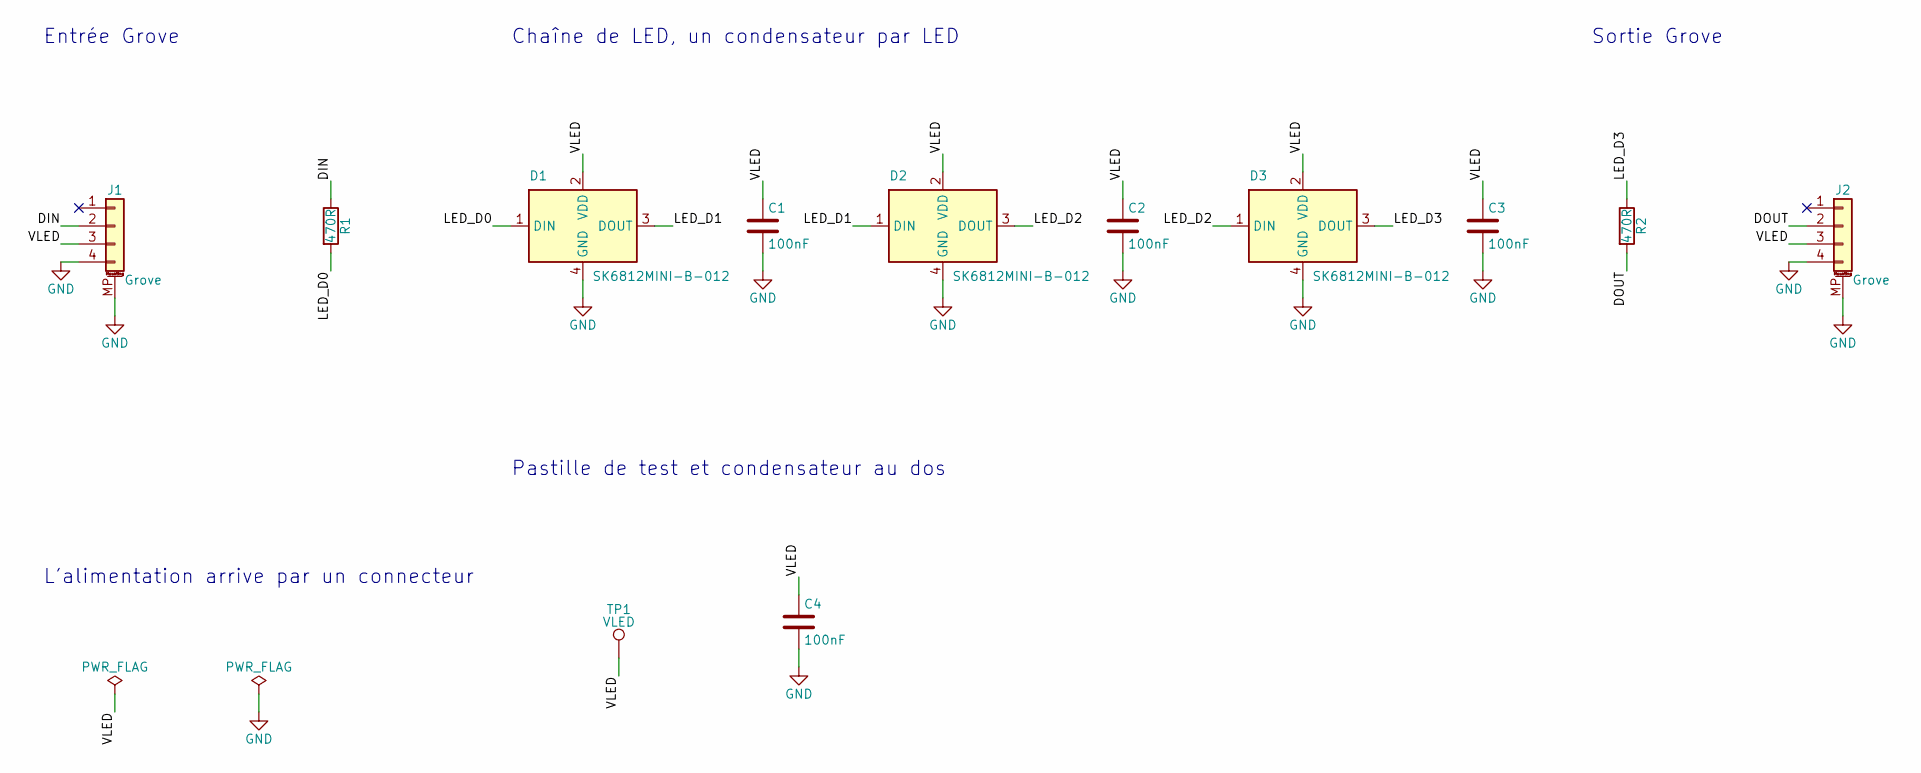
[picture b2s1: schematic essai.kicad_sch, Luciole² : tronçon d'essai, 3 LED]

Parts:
C1, C2, C3, C4: 100nF; C_0402_1005Metric; LCSC C1525
D1, D2, D3: SK6812MINI-B-012; LED_OPSCO_SK6812MINI-B-012_3.7x3.5mm; LCSC C5183448
J1, J2: Grove; Grove_HY2.0-4P_Megastar_ZX-HY2.0-4PWT_Horizontal; LCSC C7429571
R1, R2: 470R; R_0402_1005Metric; LCSC C25117
TP1: VLED; TestPoint_Pad_D1.5mm

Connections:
/DIN: J1.2, R1.1
/DOUT: J2.2, R2.2
/LED_D0: D1.1 (DIN), R1.2
/LED_D1: D1.3 (DOUT), D2.1 (DIN)
/LED_D2: D2.3 (DOUT), D3.1 (DIN)
/LED_D3: D3.3 (DOUT), R2.1
/VLED: C1.1, C2.1, C3.1, C4.1, D1.2 (VDD), D2.2 (VDD), D3.2 (VDD), J1.3, J2.3, TP1.1
GND: C1.2, C2.2, C3.2, C4.2, D1.4 (GND), D2.4 (GND), D3.4 (GND), J1.4, J1.MP (MountPin), J2.4, J2.MP (MountPin)

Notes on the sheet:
Entrée Grove
Chaîne de LED, un condensateur par LED
Sortie Grove
Pastille de test et condensateur au dos
L'alimentation arrive par un connecteur

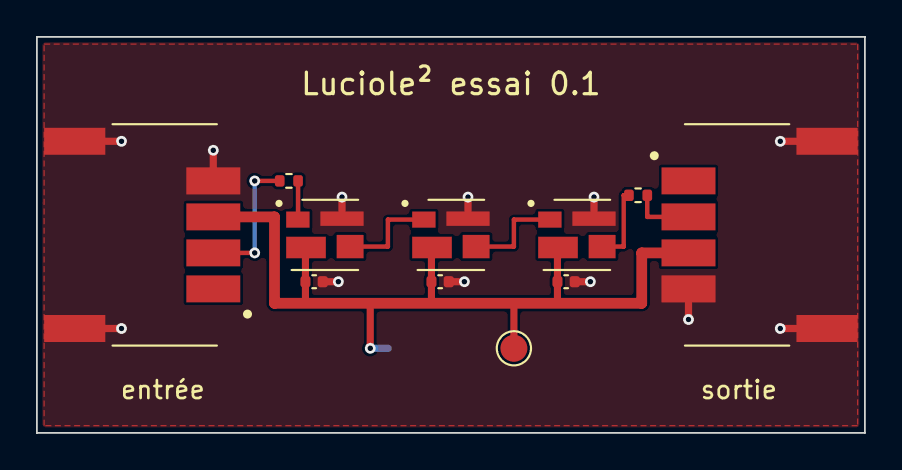
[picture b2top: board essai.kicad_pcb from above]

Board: 2 copper layers, 46.0 x 22.0 mm, 12 parts (1 on the bottom side), 8 nets.
